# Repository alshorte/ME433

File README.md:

# ME 433: Contents

## Homework 1: Making a PIC32 Cicuit From Scratch

Circuit is designed and built. PIC32 is programmed to turn on the LED, then wait for 0.5 mS to pass, then turn off the LED, then wait another 0.5 mS. Button included to pause the program until unpressed.

## Homework 2/3:

### HW2

Make a library of components for your board, draw the schematic, and start the board layout. See hw2.lib, hw2.sch

### HW3

Complete PCB. Design the .brd file, run the error checker, make the Gerber files, and check the Gerber files on another website. See PIC32_AShorter.zip for all Gerber files.

## Homework 4:

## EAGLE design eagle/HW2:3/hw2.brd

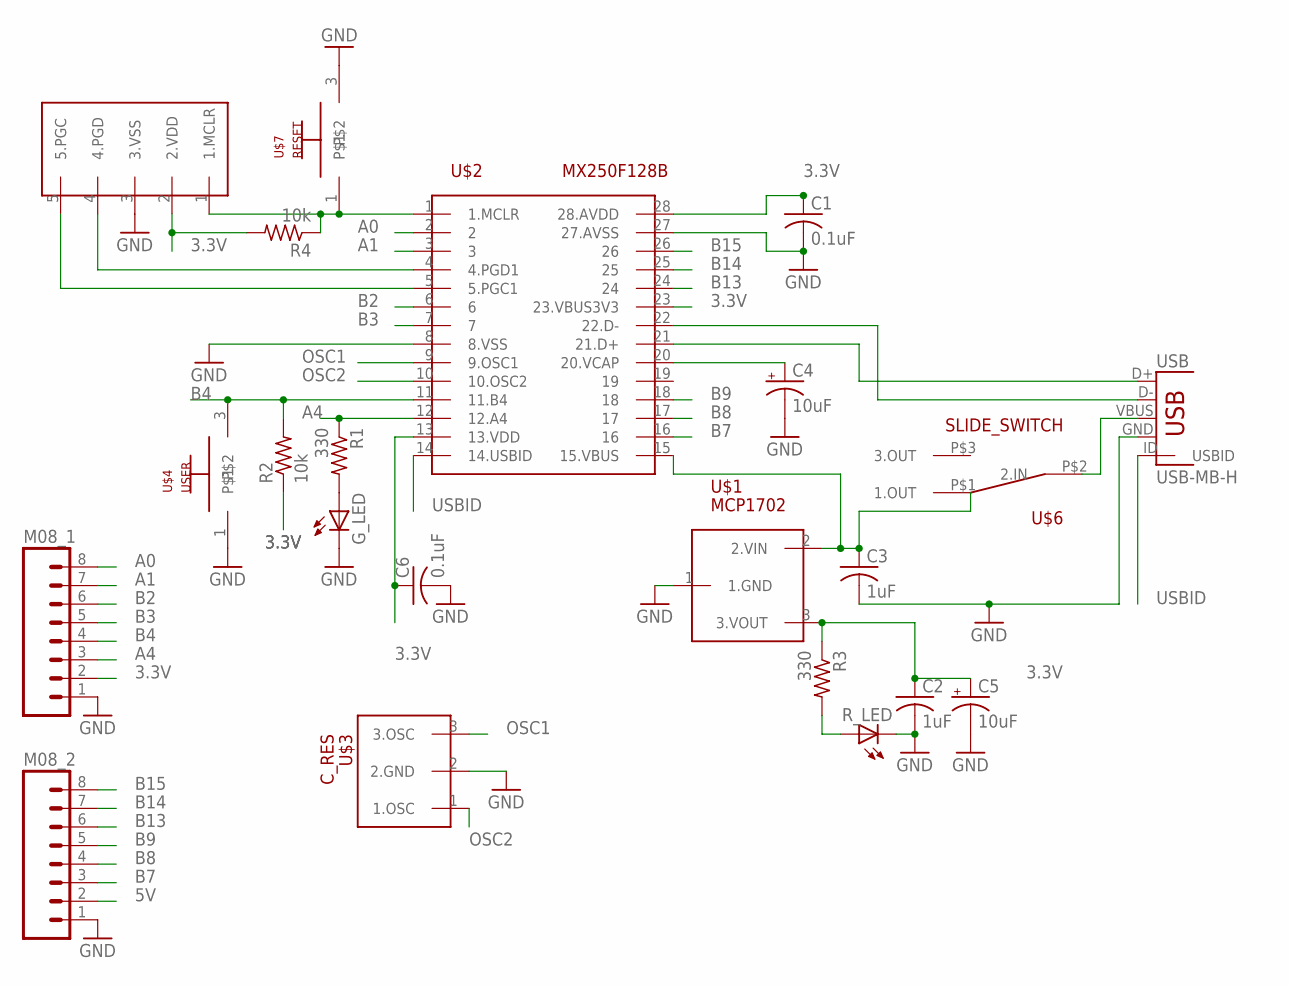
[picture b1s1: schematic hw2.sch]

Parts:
C1, C6: 0.1uF; C025-025X050
C2, C3: 1uF; C025-025X050
C4, C5: 10uF; E2,5-6E
G_LED: LED3MM
M08_1, M08_2: M08; 1X08_ROUND
R1, R3: 330; 0207/10
R2, R4: 10k; 0207/10
R_LED: LED3MM
U$1: MCP1702; TO92
U$2: MX250F128B; DIL28-3
U$3: C_RES; 1X03
U$4: USER; 1X03
U$5: PICKIT3; 1X05
U$6: SLIDE_SWITCH
U$7: RESET; 1X03
USB: USB-MB-H

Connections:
3.3V: C1.1, C2.1, C5.+, C6.1, M08_1.2, R2.1, R3.1, R4.2, U$1.3 (3.VOUT), U$2.13 (13.VDD), U$2.23 (23.VBUS3V3), U$2.28 (28.AVDD), U$5.2 (2.VDD)
5V: C3.1, M08_2.2, U$1.2 (2.VIN), U$2.15 (15.VBUS), U$2.22 (22.D-), U$6.P$1 (1.OUT), USB.D-
A0: M08_1.8, U$2.2
A1: M08_1.7, U$2.3
A4: M08_1.3, R1.1, U$2.12 (12.A4)
B2: M08_1.6, U$2.6
B3: M08_1.5, U$2.7
B4: M08_1.4, R2.2, U$2.11 (11.B4), U$4.3
B7: M08_2.3, U$2.16
B8: M08_2.4, U$2.17
B9: M08_2.5, U$2.18
B13: M08_2.6, U$2.24
B14: M08_2.7, U$2.25
B15: M08_2.8, U$2.26
GND: C1.2, C2.2, C3.2, C4.-, C5.-, C6.2, G_LED.K (C), M08_1.1, M08_2.1, R_LED.K (C), U$1.1 (1.GND), U$2.8 (8.VSS), U$2.27 (27.AVSS), U$3.2 (2.GND), U$4.1, U$5.3 (3.VSS), U$7.3, USB.GND
unnamed: U$6.P$2 (2.IN), USB.VBUS
unnamed: G_LED.A, R1.2
unnamed: U$2.21 (21.D+), USB.D+
unnamed: R3.2, R_LED.A
unnamed: C4.+, U$2.20 (20.VCAP)
unnamed: U$2.4 (4.PGD1), U$5.4 (4.PGD)
unnamed: U$2.5 (5.PGC1), U$5.5 (5.PGC)
OSC1: U$2.9 (9.OSC1), U$3.3 (3.OSC)
OSC2: U$2.10 (10.OSC2), U$3.1 (1.OSC)
RESET: R4.1, U$2.1 (1.MCLR), U$5.1 (1.MCLR), U$7.1
USBID: U$2.14 (14.USBID), USB.ID (USBID)

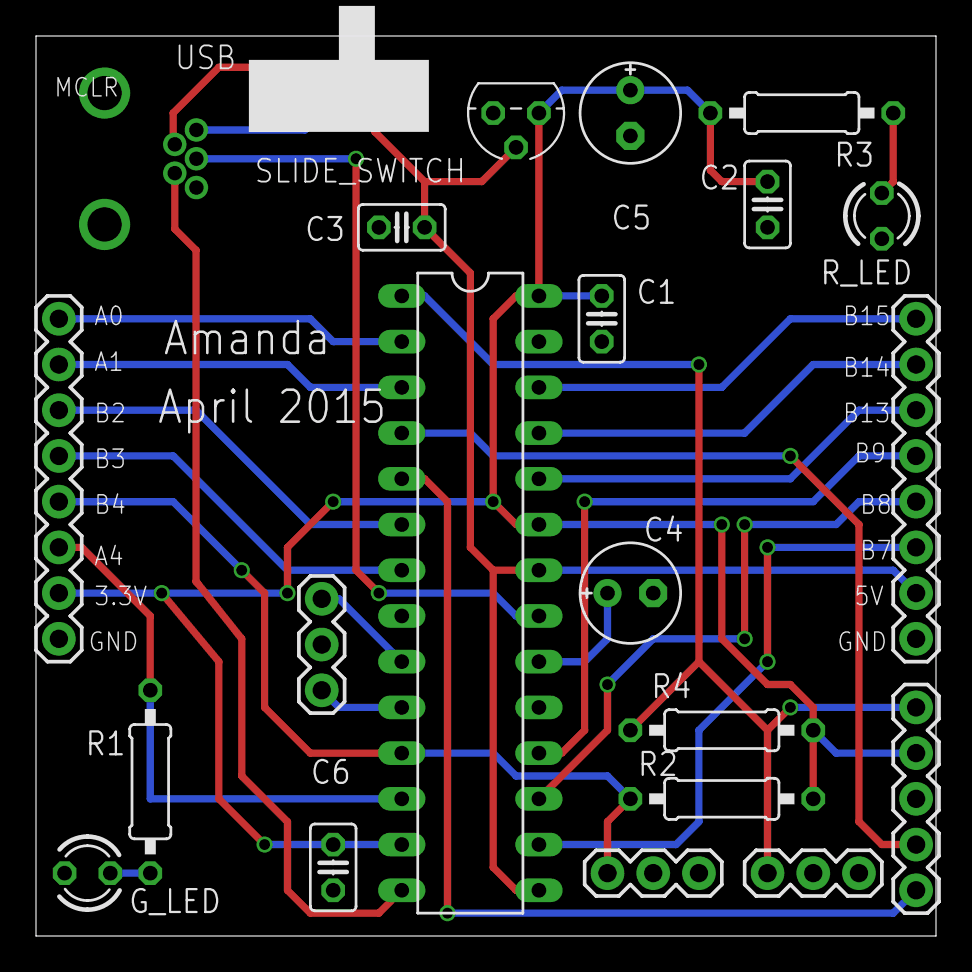
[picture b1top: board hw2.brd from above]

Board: 2 copper layers, 50.0 x 50.0 mm, 22 parts (0 on the bottom side), 26 nets.

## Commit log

2016-04-03 add README for HW1
2016-04-03 pictures for hw1 cicuit and first main.c commit
2016-04-03 add template to main.c
2016-04-04 configure DEVCFG0
2016-04-04 configure DEVCFG1
2016-04-04 configure DEVCFG3
2016-04-04 all DEVCFGx registers configured
2016-04-05 program complete
2016-04-05 Update README and README_hw1
2016-04-06 add updated pictures
2016-04-13 homework 2 and 3 complete: schematic, board, and gerber files generated
2016-04-14 update README and Archive previous .lib, .sch, and .brd files
2016-04-14 add spi template to main.c, remove spi initialization functions and put in init_com.c with the i2c initialization functions. TO DO: change main.c and init_com as required for our chip setup, add i2c 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
2016-04-19 SPI working, currently writting wave forms
2016-04-21 SPI complete, I2C initial code writteen to be tested
2016-04-21 creted i2c read and write functions, expander initialization function complete
2016-04-21 i2c code complete, for some reason the wrong led changes then the button in pressed...
2016-04-22 hw4 complete
2016-04-28 IMU code complete, ask Nick about DEV_CONFIG.h error, confirm output is as expected
2016-05-05 IMU is being read, PWM are output correctly, but do not change with changing IMU orientation... will program LCD and debug further using that
2016-05-09 start LCD code: write required functions, need to figureout ehat to pass
2016-05-10 fix DEV_CONFIG.h file (need to replace all previous hm instances), LCD cond compiles, but nothing shows up on LCD
2016-05-10 hw5 complete, fixed DEV_CONFIG.h added to all previous hw
2016-05-12 complete HW9: Android slider bar app
2016-05-12 add pictures of output for hw 4, 5, and 6. complete hw6 (need to adjust to do multiple read to run faster)
2016-05-12 remove unnecessary functions from hw4 used for debugging hw6
2016-06-03 homework 8 complete
2016-06-04 added content for HW11 and HW12 to repository
2016-06-08 added Android code (HW14), pic code (HW15), and results.txt (HW16)
2016-06-09 HW7 complete
